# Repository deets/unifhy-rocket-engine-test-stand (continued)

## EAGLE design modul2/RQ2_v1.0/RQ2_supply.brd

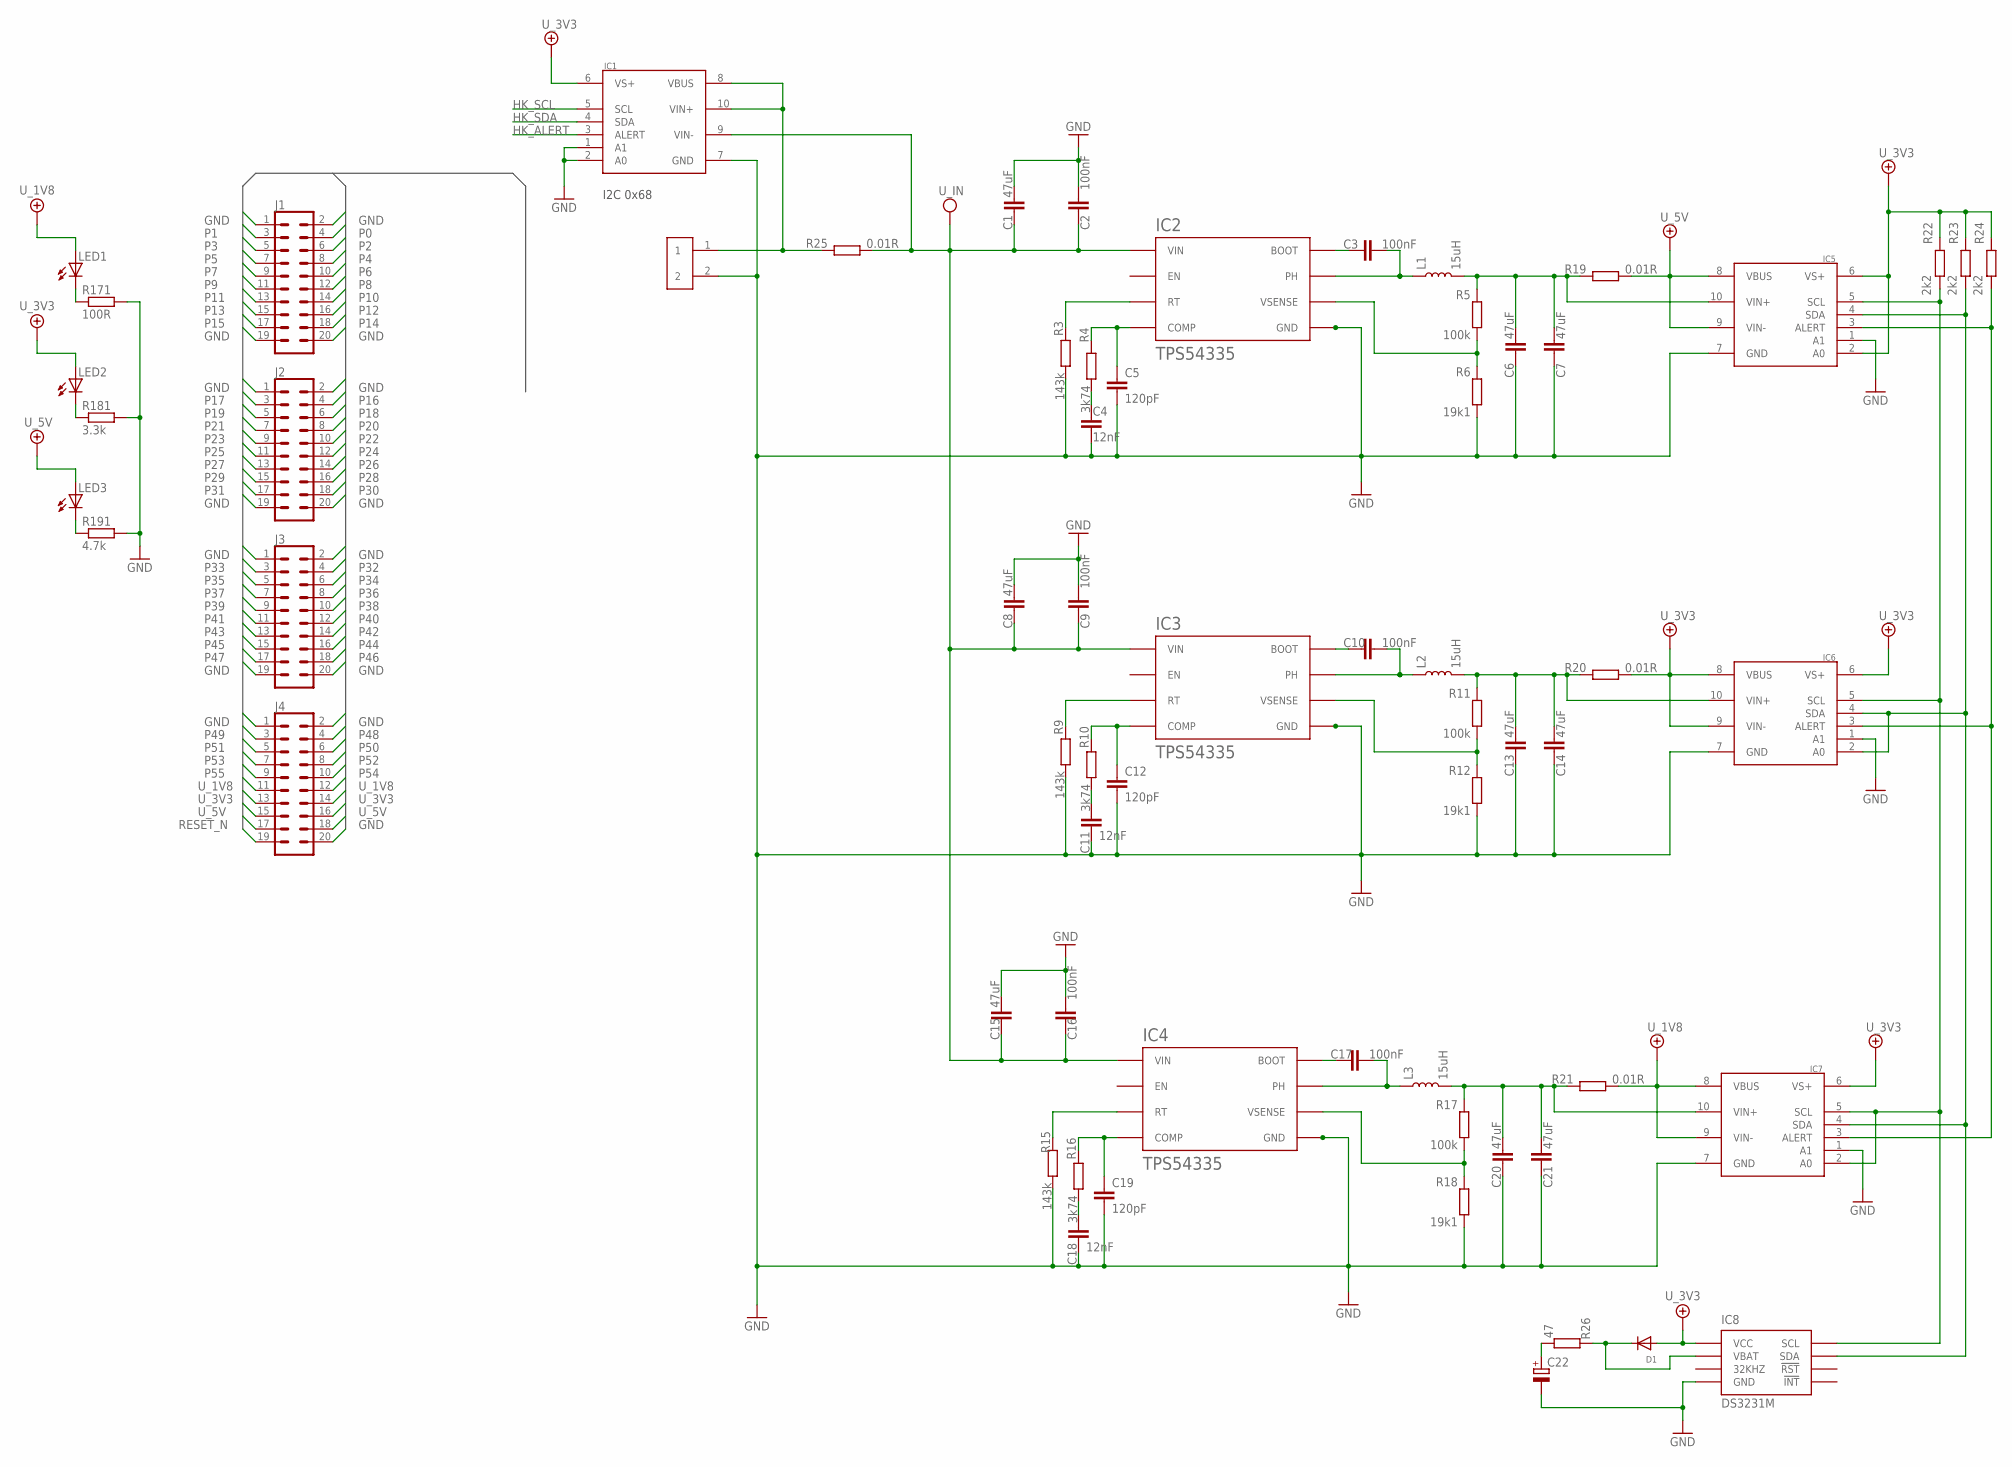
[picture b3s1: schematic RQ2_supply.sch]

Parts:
C1, C6, C7, C8, C13, C14, C15, C20, C21: 47uF; 1206
C2, C9, C16: 100nF; 0603
C3, C10, C17: 100nF; 0402
C4, C11, C18: 12nF; C0402
C5, C12, C19: 120pF; C0402
C22: CPOL-EUDHL_21.5; DHL_21.5
D1: DIODESOD-123; SOD-123
IC1, IC5, IC6, IC7: INA226; VSSOP-10
IC2, IC3, IC4: TPS54335ADRCR; VSON-10
IC8: DS3231M; SO-8
J1, J2, J3, J4: CONN_10X2; 2X10
L1, L2, L3: 15uH; YSPIA0850
LED1, LED2, LED3: LEDSML0805; SML0805
R3, R9, R15: 143k; R0402
R4, R10, R16: 3k74; R0402
R5, R11, R17: 100k; R0402
R6, R12, R18: 19k1; R0402
R19, R20, R21, R25: 0.01R; R1206
R22, R23, R24: 2k2; R0402
R26: 47; R0603
R171: 100R; R0805
R181: 3.3k; R0805
R191: 4.7k; R0805
U$1: XT_CONN; XT30_PCB

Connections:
DCDC_BOOT: C3.2, IC2.9 (BOOT)
DCDC_BOOT1: C10.2, IC3.9 (BOOT)
DCDC_BOOT2: C17.2, IC4.9 (BOOT)
DCDC_COMP: C5.1, IC2.7 (COMP), R4.1
DCDC_COMP1: C12.1, IC3.7 (COMP), R10.1
DCDC_COMP2: C19.1, IC4.7 (COMP), R16.1
DCDC_PH: C3.1, IC2.2 (PH), L1.1
DCDC_PH1: C10.1, IC3.2 (PH), L2.1
DCDC_PH2: C17.1, IC4.2 (PH), L3.1
DCDC_RT: IC2.10 (RT), R3.1
DCDC_RT1: IC3.10 (RT), R9.1
DCDC_RT2: IC4.10 (RT), R15.1
GND: C1.2, C2.1, C4.2, C5.2, C6.1, C7.1, C8.2, C9.1, C11.2, C12.2, C13.1, C14.1, C15.2, C16.1, C18.2, C19.2, C20.1, C21.1, C22.-, IC1.1 (A1), IC1.2 (A0), IC1.7 (GND), IC2.3 (GND), IC2.4 (GND), IC2.5 (GND), IC2.11 (GND), IC3.3 (GND), IC3.4 (GND), IC3.5 (GND), IC3.11 (GND), IC4.3 (GND), IC4.4 (GND), IC4.5 (GND), IC4.11 (GND), IC5.1 (A1), IC5.7 (GND), IC6.1 (A1), IC6.7 (GND), IC7.1 (A1), IC7.7 (GND), IC8.5 (GND), J1.1, J1.2, J1.19, J1.20, J2.1, J2.2, J2.19, J2.20, J3.1, J3.2, J3.19, J3.20, J4.1, J4.2, J4.18, R3.2, R6.1, R9.2, R12.1, R15.2, R18.1, R171.2, R181.2, R191.2, U$1.2
HK_ALERT: IC1.3 (ALERT), IC5.3 (ALERT), IC6.3 (ALERT), IC7.3 (ALERT), R24.1
HK_SCL: IC1.5 (SCL), IC5.5 (SCL), IC6.5 (SCL), IC7.2 (A0), IC7.5 (SCL), IC8.8 (SCL), R22.1
HK_SDA: IC1.4 (SDA), IC5.4 (SDA), IC6.2 (A0), IC6.4 (SDA), IC7.4 (SDA), IC8.7 (SDA), R23.1
unnamed: C4.1, R4.2
unnamed: LED1.C, R171.1
unnamed: LED2.C, R181.1
unnamed: LED3.C, R191.1
unnamed: C11.1, R10.2
unnamed: C18.1, R16.2
P0: J1.4
P1: J1.3
P2: J1.6
P3: J1.5
P4: J1.8
P5: J1.7
P6: J1.10
P7: J1.9
P8: J1.12
P9: J1.11
P10: J1.14
P11: J1.13
P12: J1.16
P13: J1.15
P14: J1.18
P15: J1.17
P16: J2.4
P17: J2.3
P18: J2.6
P19: J2.5
P20: J2.8
P21: J2.7
P22: J2.10
P23: J2.9
P24: J2.12
P25: J2.11
P26: J2.14
P27: J2.13
P28: J2.16
P29: J2.15
P30: J2.18
P31: J2.17
P32: J3.4
P33: J3.3
P34: J3.6
P35: J3.5
P36: J3.8
P37: J3.7
P38: J3.10
P39: J3.9
P40: J3.12
P41: J3.11
P42: J3.14
P43: J3.13
P44: J3.16
P45: J3.15
P46: J3.18
P47: J3.17
P48: J4.4
P49: J4.3
P50: J4.6
P51: J4.5
P52: J4.8
P53: J4.7
P54: J4.10
P55: J4.9
RESET_N: J4.17
RXD: J4.20
TXD: J4.19
U0_1V8: C20.2, C21.2, IC7.10 (VIN+), L3.2, R17.2, R21.2
U0_3V3: C13.2, C14.2, IC6.10 (VIN+), L2.2, R11.2, R20.2
U0_5V: C6.2, C7.2, IC5.10 (VIN+), L1.2, R5.2, R19.2
U0_IN: IC1.8 (VBUS), IC1.10 (VIN+), R25.2, U$1.1
U_1V8: IC7.8 (VBUS), IC7.9 (VIN-), J4.11, J4.12, LED1.A, R21.1
U_3V3: D1.A, IC5.2 (A0), IC6.6 (VS+), IC6.8 (VBUS), IC6.9 (VIN-), IC7.6 (VS+), IC8.2 (VCC), J4.13, J4.14, LED2.A, R20.1, R22.2, R23.2, R24.2
U_5V: IC5.8 (VBUS), IC5.9 (VIN-), J4.15, J4.16, LED3.A, R19.1
U_IN: C1.1, C2.2, C8.1, C9.2, C15.1, C16.2, IC1.9 (VIN-), IC2.1 (VIN), IC3.1 (VIN), IC4.1 (VIN), R25.1
VBAT1: D1.C, IC8.6 (VBAT), R26.1
VCAP: C22.+, R26.2
VSENSE_1V8: IC4.6 (VSENSE), R17.1, R18.2
VSENSE_3V3: IC3.6 (VSENSE), R11.1, R12.2
VSENSE_5V: IC2.6 (VSENSE), R5.1, R6.2

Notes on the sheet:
I2C 0x68

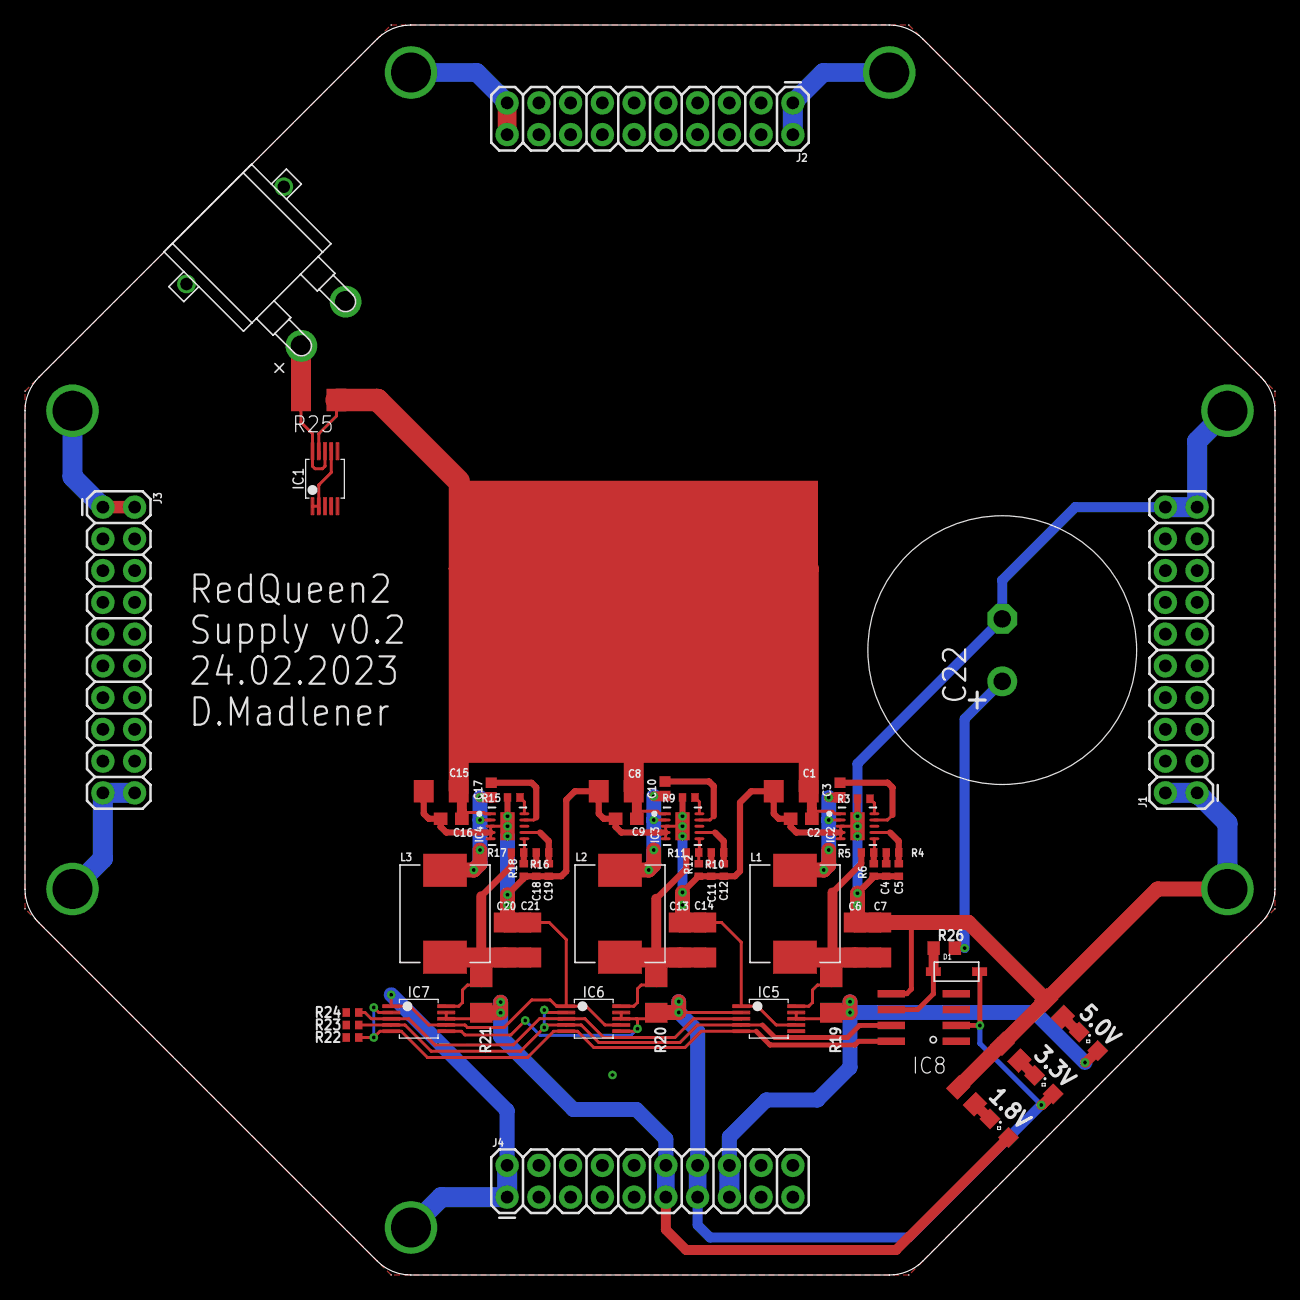
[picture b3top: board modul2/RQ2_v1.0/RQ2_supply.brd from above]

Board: 2 copper layers, 100.0 x 100.0 mm, 65 parts (0 on the bottom side), 35 nets.

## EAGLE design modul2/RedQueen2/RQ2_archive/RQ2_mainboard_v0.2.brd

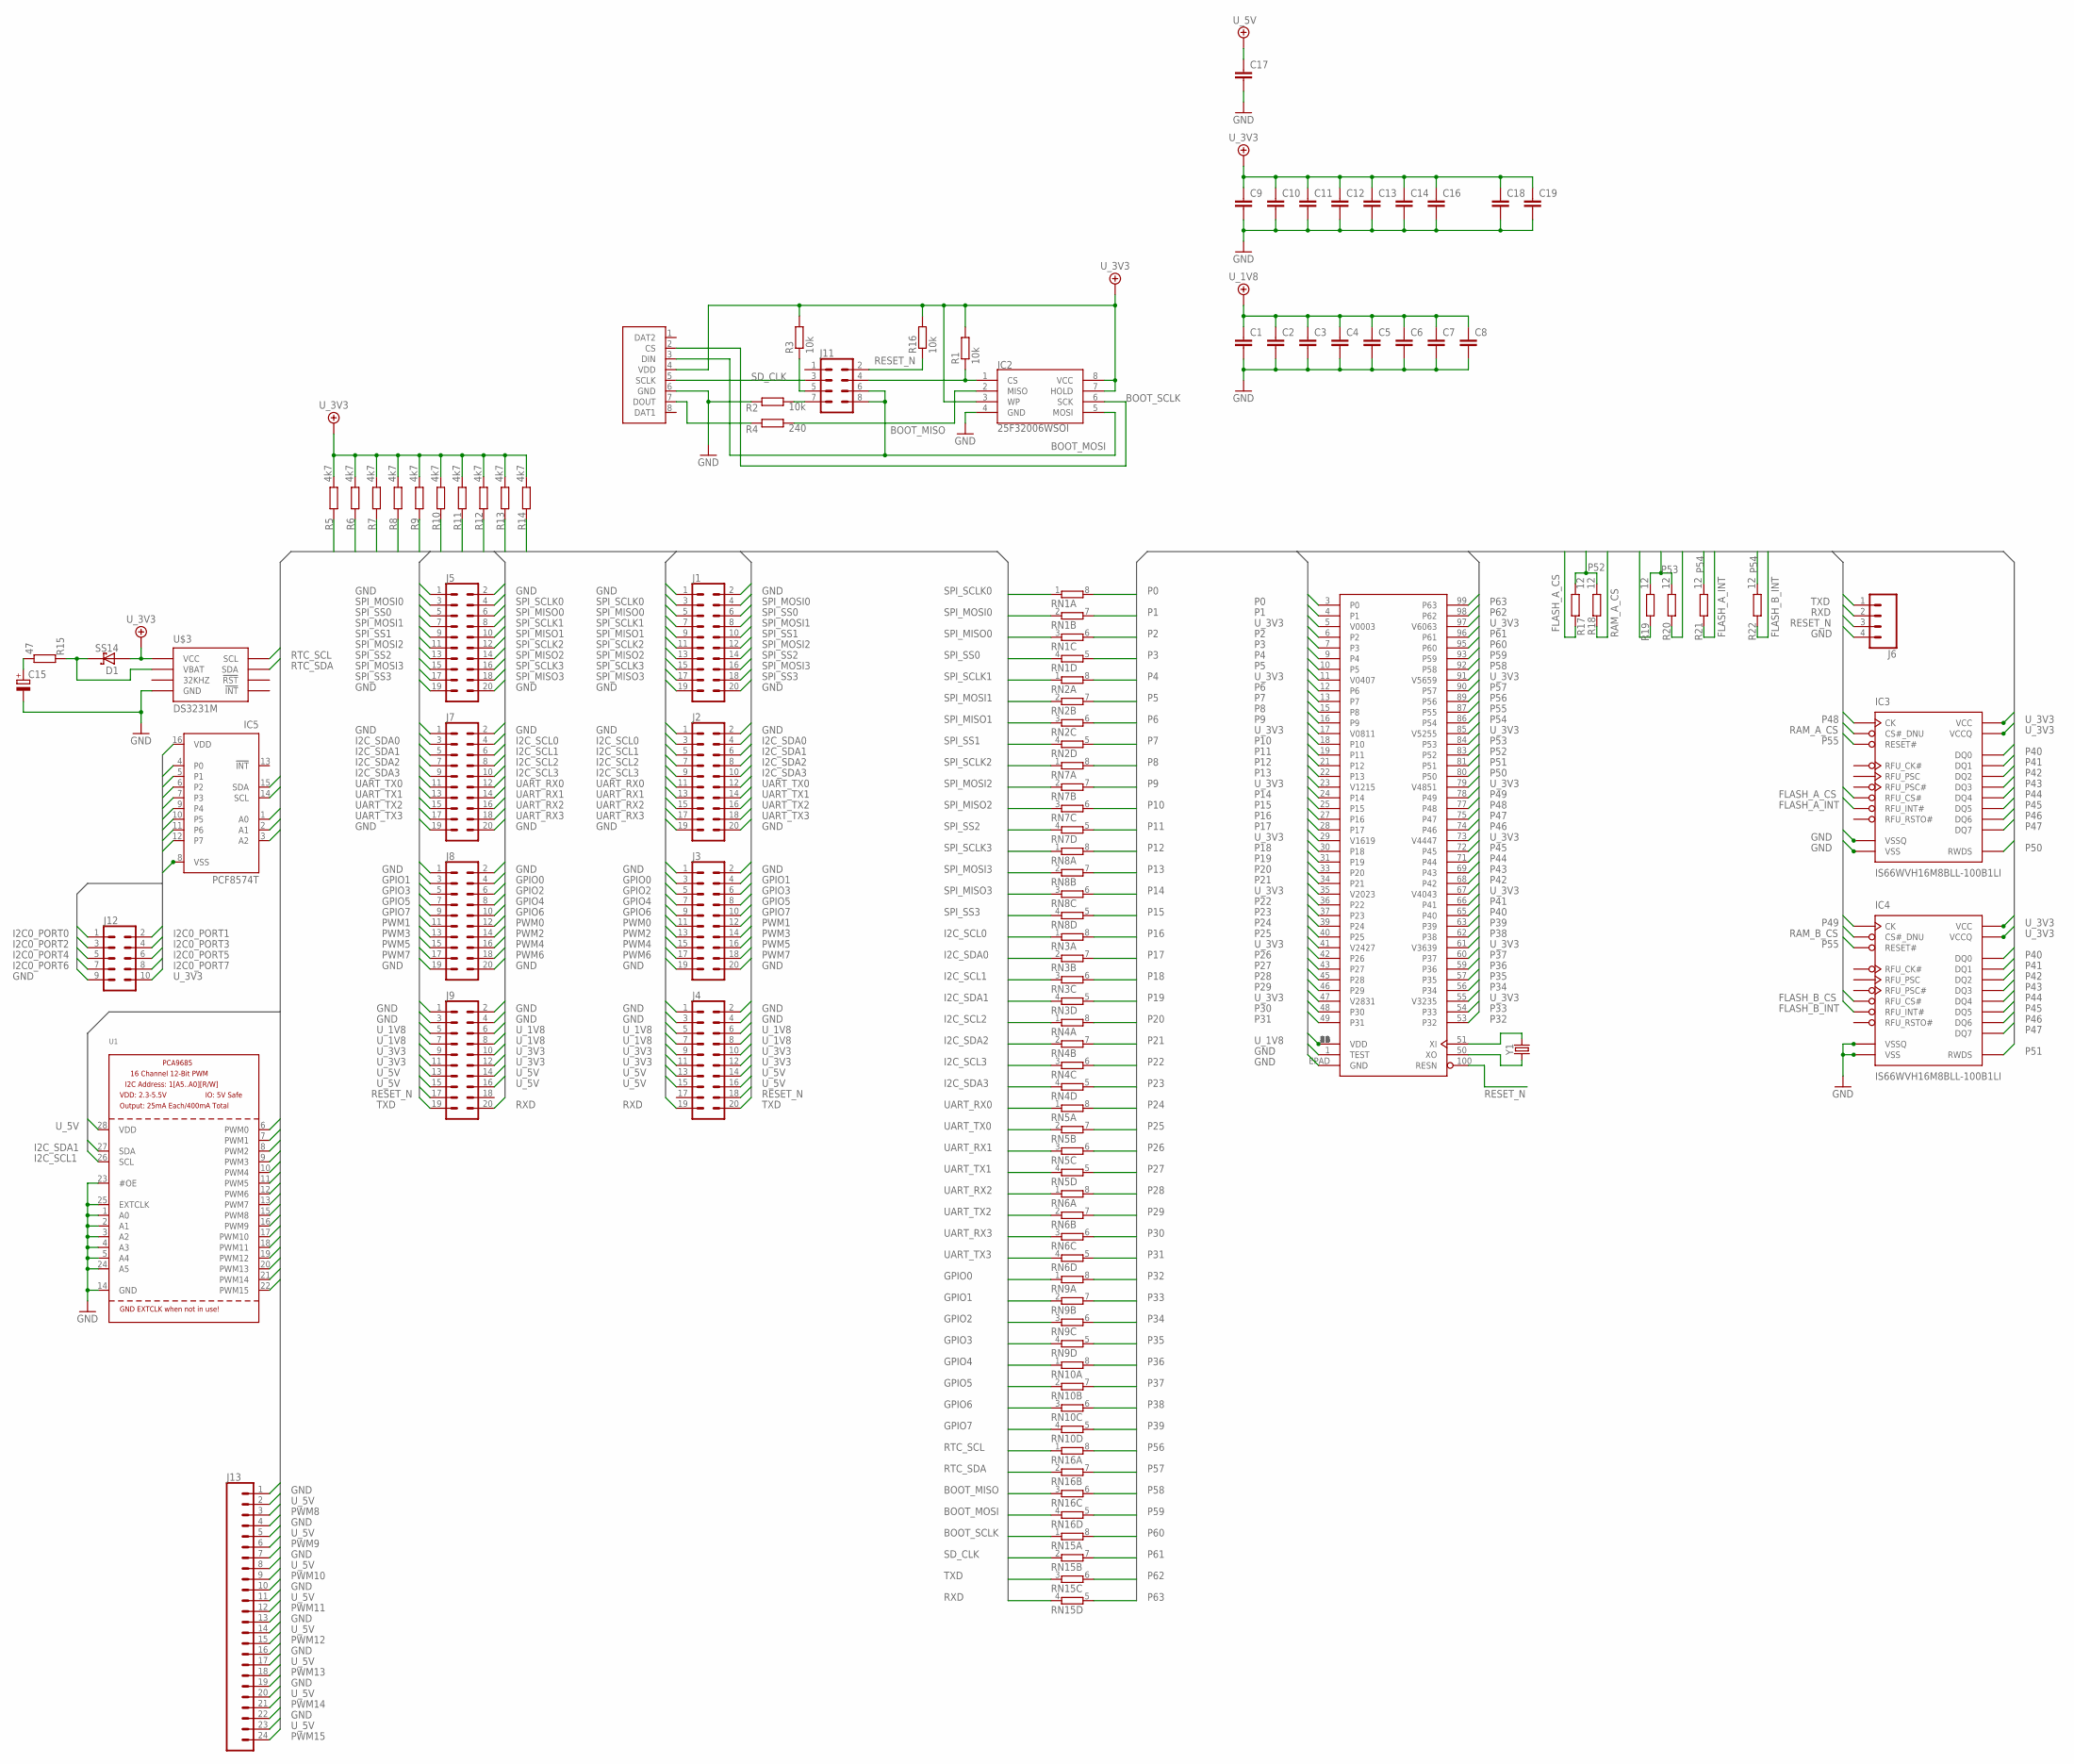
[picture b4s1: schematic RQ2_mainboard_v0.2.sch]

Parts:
C1, C2, C3, C4, C5, C6, C7, C8, C9, C10, C11, C12, C13, C14, C16, C17, C18, C19: C-EUC0805; C0805
C15: CPOL-EUDHL_21.5; DHL_21.5
D1: SS14; SMA_403D
IC1: P2X8C4M64P; TQFP100
IC2: 25F32006WSOI; SO08-EIAJ
IC3, IC4: IS66WVH16M8BLL-100B1LI; BGA-24
IC5: PCF8574T; SO16W
J1, J2, J3, J4, J5, J7, J8, J9: CONN_10X2SMT; 2X10_SMT
J6: CONN_04; 1X04
J11: CONN_04X2; 2X4
J12: CONN_05X2SHD; 2X5-SHROUDED
J13: CONN_24SERVO_8; 3X8
R1, R2, R3, R16: 10k; R0603
R4: 240; R0603
R5, R6, R7, R8, R9, R10, R11, R12, R13, R14: 4k7; R0603
R15: 47; R0603
R17, R18, R19, R20, R21, R22: 12; R0402
RN1, RN2, RN3, RN4, RN5, RN6, RN7, RN8, RN9, RN10, RN15, RN16: 4R-N0603-ARV; 0603-ARV
U1: PCA9685; TSSOP28
U$2: MICRO_SD_CONNECTORMOLEX_HINGE; MICRO_SD
U$3: DS3231M; SO-8
Y1: CRYSTALSMD-5X3.2-2PAD; CRYSTAL-SMD-5X3.2-2PAD

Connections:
BOOT_MISO: IC2.2 (MISO), R4.1, RN16.3 (1)
BOOT_MOSI: IC2.5 (MOSI), J11.6, J11.8, RN16.4 (1), U$2.3 (DIN)
BOOT_SCLK: IC2.6 (SCK), RN15.1, U$2.2 (CS)
FLASH_A_CS: IC3.C2 (RFU_CS#), R17.2
FLASH_A_INT: IC3.A5 (RFU_INT#), R21.2
FLASH_B_CS: IC4.C2 (RFU_CS#), R19.2
FLASH_B_INT: IC4.A5 (RFU_INT#), R22.2
FLASH_CS: IC2.1 (CS), J11.4, R1.1
GND: C1.2, C2.2, C3.2, C4.2, C5.2, C6.2, C7.2, C8.2, C9.2, C10.2, C11.2, C12.2, C13.2, C14.2, C15.-, C16.2, C17.2, C18.2, C19.2, IC1.1 (TEST), IC1.EPAD (GND), IC2.4 (GND), IC3.B3 (VSS), IC3.C1 (VSSQ), IC3.E5 (VSSQ), IC4.B3 (VSS), IC4.C1 (VSSQ), IC4.E5 (VSSQ), IC5.1 (A0), IC5.2 (A1), IC5.3 (A2), IC5.8 (VSS), J1.1, J1.2, J1.19, J1.20, J2.1, J2.2, J2.19, J2.20, J3.1, J3.2, J3.19, J3.20, J4.1, J4.2, J4.3, J4.4, J5.1, J5.2, J5.19, J5.20, J6.4, J7.1, J7.2, J7.19, J7.20, J8.1, J8.2, J8.19, J8.20, J9.1, J9.2, J9.3, J9.4, J12.9, J13.1, J13.4, J13.7, J13.10, J13.13, J13.16, J13.19, J13.22, R2.2, U1.1 (A0), U1.2 (A1), U1.3 (A2), U1.4 (A3), U1.5 (A4), U1.14 (GND), U1.23 (#OE), U1.24 (A5), U1.25 (EXTCLK), U$2.6 (GND), U$3.5 (GND)
GPIO0: J3.3, J8.4, RN9.1
GPIO1: J3.4, J8.3, RN9.2 (1)
GPIO2: J3.5, J8.6, RN9.3 (1)
GPIO3: J3.6, J8.5, RN9.4 (1)
GPIO4: J3.7, J8.8, RN10.1
GPIO5: J3.8, J8.7, RN10.2 (1)
GPIO6: J3.9, J8.10, RN10.3 (1)
GPIO7: J3.10, J8.9, RN10.4 (1)
I2C0_PORT0: IC5.4 (P0), J12.1
I2C0_PORT1: IC5.5 (P1), J12.2
I2C0_PORT2: IC5.6 (P2), J12.3
I2C0_PORT3: IC5.7 (P3), J12.4
I2C0_PORT4: IC5.9 (P4), J12.5
I2C0_PORT5: IC5.10 (P5), J12.6
I2C0_PORT6: IC5.11 (P6), J12.7
I2C0_PORT7: IC5.12 (P7), J12.8
I2C_SCL0: IC5.14 (SCL), J2.3, J7.4, R5.1, RN3.1
I2C_SCL1: J2.5, J7.6, R7.1, RN3.3 (1), U1.26 (SCL)
I2C_SCL2: J2.7, J7.8, R9.1, RN4.1
I2C_SCL3: J2.9, J7.10, R11.1, RN4.3 (1)
I2C_SDA0: IC5.15 (SDA), J2.4, J7.3, R6.1, RN3.2 (1)
I2C_SDA1: J2.6, J7.5, R8.1, RN3.4 (1), U1.27 (SDA)
I2C_SDA2: J2.8, J7.7, R10.1, RN4.2 (1)
I2C_SDA3: J2.10, J7.9, R12.1, RN4.4 (1)
unnamed: J11.7, R2.1
unnamed: J11.5, R3.1
unnamed: R4.2, U$2.7 (DOUT)
P0: IC1.3 (P0), RN1.8 (2)
P1: IC1.4 (P1), RN1.7 (2)
P2: IC1.6 (P2), RN1.6 (2)
P3: IC1.7 (P3), RN1.5 (2)
P4: IC1.9 (P4), RN2.8 (2)
P5: IC1.10 (P5), RN2.7 (2)
P6: IC1.12 (P6), RN2.6 (2)
P7: IC1.13 (P7), RN2.5 (2)
P8: IC1.15 (P8), RN7.8 (2)
P9: IC1.16 (P9), RN7.7 (2)
P10: IC1.18 (P10), RN7.6 (2)
P11: IC1.19 (P11), RN7.5 (2)
P12: IC1.21 (P12), RN8.8 (2)
P13: IC1.22 (P13), RN8.7 (2)
P14: IC1.24 (P14), RN8.6 (2)
P15: IC1.25 (P15), RN8.5 (2)
P16: IC1.27 (P16), RN3.8 (2)
P17: IC1.28 (P17), RN3.7 (2)
P18: IC1.30 (P18), RN3.6 (2)
P19: IC1.31 (P19), RN3.5 (2)
P20: IC1.33 (P20), RN4.8 (2)
P21: IC1.34 (P21), RN4.7 (2)
P22: IC1.36 (P22), RN4.6 (2)
P23: IC1.37 (P23), RN4.5 (2)
P24: IC1.39 (P24), RN5.8 (2)
P25: IC1.40 (P25), RN5.7 (2)
P26: IC1.42 (P26), RN5.6 (2)
P27: IC1.43 (P27), RN5.5 (2)
P28: IC1.45 (P28), RN6.8 (2)
P29: IC1.46 (P29), RN6.7 (2)
P30: IC1.48 (P30), RN6.6 (2)
P31: IC1.49 (P31), RN6.5 (2)
P32: IC1.53 (P32), RN9.8 (2)
P33: IC1.54 (P33), RN9.7 (2)
P34: IC1.56 (P34), RN9.6 (2)
P35: IC1.57 (P35), RN9.5 (2)
P36: IC1.59 (P36), RN10.8 (2)
P37: IC1.60 (P37), RN10.7 (2)
P38: IC1.62 (P38), RN10.6 (2)
P39: IC1.63 (P39), RN10.5 (2)
P40: IC1.65 (P40), IC3.D3 (DQ0), IC4.D3 (DQ0)
P41: IC1.66 (P41), IC3.D2 (DQ1), IC4.D2 (DQ1)
P42: IC1.68 (P42), IC3.C4 (DQ2), IC4.C4 (DQ2)
P43: IC1.69 (P43), IC3.D4 (DQ3), IC4.D4 (DQ3)
P44: IC1.71 (P44), IC3.D5 (DQ4), IC4.D5 (DQ4)
P45: IC1.72 (P45), IC3.E3 (DQ5), IC4.E3 (DQ5)
P46: IC1.74 (P46), IC3.E2 (DQ6), IC4.E2 (DQ6)
P47: IC1.75 (P47), IC3.E1 (DQ7), IC4.E1 (DQ7)
P48: IC1.77 (P48), IC3.B2 (CK)
P49: IC1.78 (P49), IC4.B2 (CK)
P50: IC1.80 (P50), IC3.C3 (RWDS)
P51: IC1.81 (P51), IC4.C3 (RWDS)
P52: IC1.83 (P52), R17.1, R18.1
P53: IC1.84 (P53), R19.1, R20.1
P54: IC1.86 (P54), R21.1, R22.1
P55: IC1.87 (P55), IC3.A4 (RESET#), IC4.A4 (RESET#)
P56: IC1.89 (P56), RN16.8 (2)
P57: IC1.90 (P57), RN16.7 (2)
P58: IC1.92 (P58), RN16.6 (2)
P59: IC1.93 (P59), RN16.5 (2)
P60: IC1.95 (P60), RN15.8 (2)
P61: IC1.96 (P61), RN15.7 (2)
P62: IC1.98 (P62), RN15.6 (2)
P63: IC1.99 (P63), RN15.5 (2)
PWM0: J3.11, J8.12, U1.6 (PWM0)
PWM1: J3.12, J8.11, U1.7 (PWM1)
PWM2: J3.13, J8.14, U1.8 (PWM2)
PWM3: J3.14, J8.13, U1.9 (PWM3)
PWM4: J3.15, J8.16, U1.10 (PWM4)
PWM5: J3.16, J8.15, U1.11 (PWM5)
PWM6: J3.17, J8.18, U1.12 (PWM6)
PWM7: J3.18, J8.17, U1.13 (PWM7)
PWM8: J13.3, U1.15 (PWM8)
PWM9: J13.6, U1.16 (PWM9)
PWM10: J13.9, U1.17 (PWM10)
PWM11: J13.12, U1.18 (PWM11)
PWM12: J13.15, U1.19 (PWM12)
PWM13: J13.18, U1.20 (PWM13)
PWM14: J13.21, U1.21 (PWM14)
PWM15: J13.24, U1.22 (PWM15)
RAM_A_CS: IC3.A3 (CS#_DNU), R18.2
RAM_B_CS: IC4.A3 (CS#_DNU), R20.2
RESET_N: IC1.100 (RESN), J4.18, J6.3, J9.17, J11.2, R16.1
RTC_SCL: R13.1, RN16.1, U$3.8 (SCL)
RTC_SDA: R14.1, RN16.2 (1), U$3.7 (SDA)
RXD: J4.19, J6.2, J9.20, RN15.4 (1)
SD_CLK: J11.3, RN15.2 (1), U$2.5 (SCLK)
SPI_MISO0: J1.5, J5.6, RN1.3 (1)
SPI_MISO1: J1.9, J5.10, RN2.3 (1)
SPI_MISO2: J1.13, J5.14, RN7.3 (1)
SPI_MISO3: J1.17, J5.18, RN8.3 (1)
SPI_MOSI0: J1.4, J5.3, RN1.2 (1)
SPI_MOSI1: J1.8, J5.7, RN2.2 (1)
SPI_MOSI2: J1.12, J5.11, RN7.2 (1)
SPI_MOSI3: J1.16, J5.15, RN8.2 (1)
SPI_SCLK0: J1.3, J5.4, RN1.1
SPI_SCLK1: J1.7, J5.8, RN2.1
SPI_SCLK2: J1.11, J5.12, RN7.1
SPI_SCLK3: J1.15, J5.16, RN8.1
SPI_SS0: J1.6, J5.5, RN1.4 (1)
SPI_SS1: J1.10, J5.9, RN2.4 (1)
SPI_SS2: J1.14, J5.13, RN7.4 (1)
SPI_SS3: J1.18, J5.17, RN8.4 (1)
TXD: J4.20, J6.1, J9.19, RN15.3 (1)
UART_RX0: J2.11, J7.12, RN5.1
UART_RX1: J2.13, J7.14, RN5.3 (1)
UART_RX2: J2.15, J7.16, RN6.1
UART_RX3: J2.17, J7.18, RN6.3 (1)
UART_TX0: J2.12, J7.11, RN5.2 (1)
UART_TX1: J2.14, J7.13, RN5.4 (1)
UART_TX2: J2.16, J7.15, RN6.2 (1)
UART_TX3: J2.18, J7.17, RN6.4 (1)
U_1V8: C1.1, C2.1, C3.1, C4.1, C5.1, C6.1, C7.1, C8.1, IC1.2 (VDD), IC1.8 (VDD), IC1.14 (VDD), IC1.20 (VDD), IC1.26 (VDD), IC1.32 (VDD), IC1.38 (VDD), IC1.44 (VDD), IC1.52 (VDD), IC1.58 (VDD), IC1.64 (VDD), IC1.70 (VDD), IC1.76 (VDD), IC1.82 (VDD), IC1.88 (VDD), IC1.94 (VDD), J4.5, J4.6, J4.7, J4.8, J9.5, J9.6, J9.7, J9.8
U_3V3: C9.1, C10.1, C11.1, C12.1, C13.1, C14.1, C16.1, C18.1, C19.1, D1.A, IC1.5 (V0003), IC1.11 (V0407), IC1.17 (V0811), IC1.23 (V1215), IC1.29 (V1619), IC1.35 (V2023), IC1.41 (V2427), IC1.47 (V2831), IC1.55 (V3235), IC1.61 (V3639), IC1.67 (V4043), IC1.73 (V4447), IC1.79 (V4851), IC1.85 (V5255), IC1.91 (V5659), IC1.97 (V6063), IC2.3 (WP), IC2.7 (HOLD), IC2.8 (VCC), IC3.B4 (VCC), IC3.D1 (VCCQ), IC3.E4 (VCCQ), IC4.B4 (VCC), IC4.D1 (VCCQ), IC4.E4 (VCCQ), IC5.16 (VDD), J4.9, J4.10, J4.11, J4.12, J9.9, J9.10, J9.11, J9.12, J12.10, R1.2, R3.2, R5.2, R6.2, R7.2, R8.2, R9.2, R10.2, R11.2, R12.2, R13.2, R14.2, R16.2, U$2.4 (VDD), U$3.2 (VCC)
U_5V: C17.1, J4.13, J4.14, J4.15, J4.16, J9.13, J9.14, J9.15, J9.16, J13.2, J13.5, J13.8, J13.11, J13.14, J13.17, J13.20, J13.23, U1.28 (VDD)
VBAT: D1.C, R15.1, U$3.6 (VBAT)
VCAP: C15.+, R15.2
XIN: IC1.51 (XI), Y1.P$2 (2)
XOUT: IC1.50 (XO), Y1.P$1 (1)

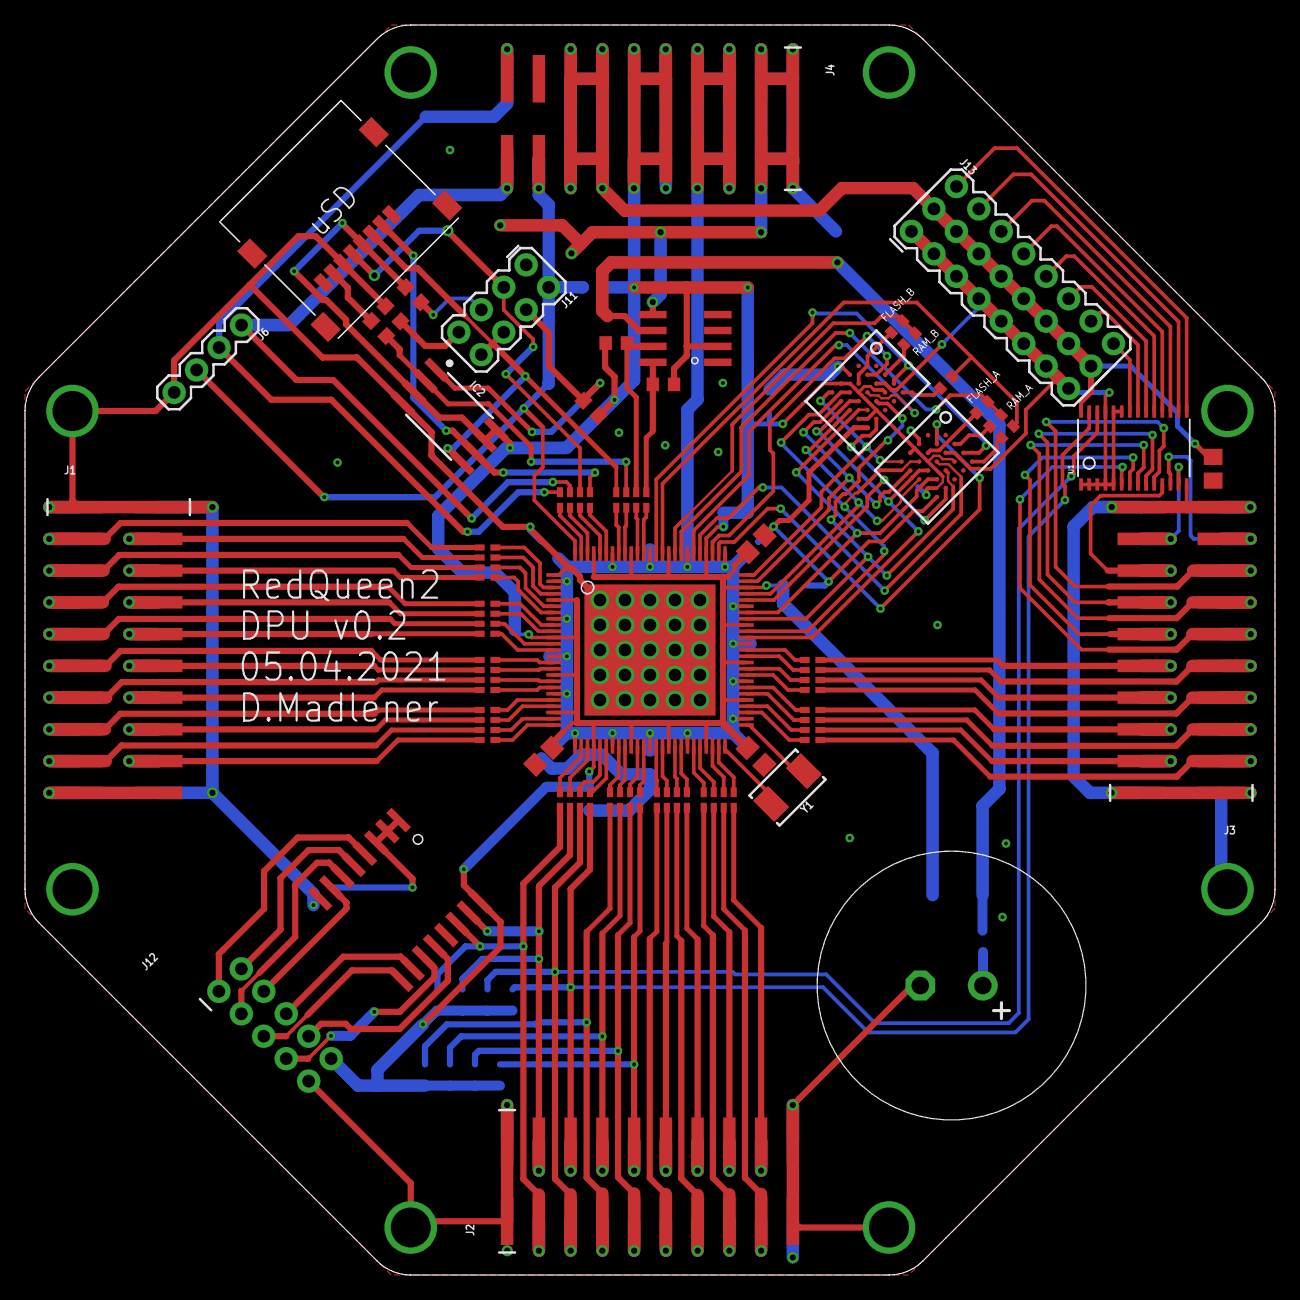
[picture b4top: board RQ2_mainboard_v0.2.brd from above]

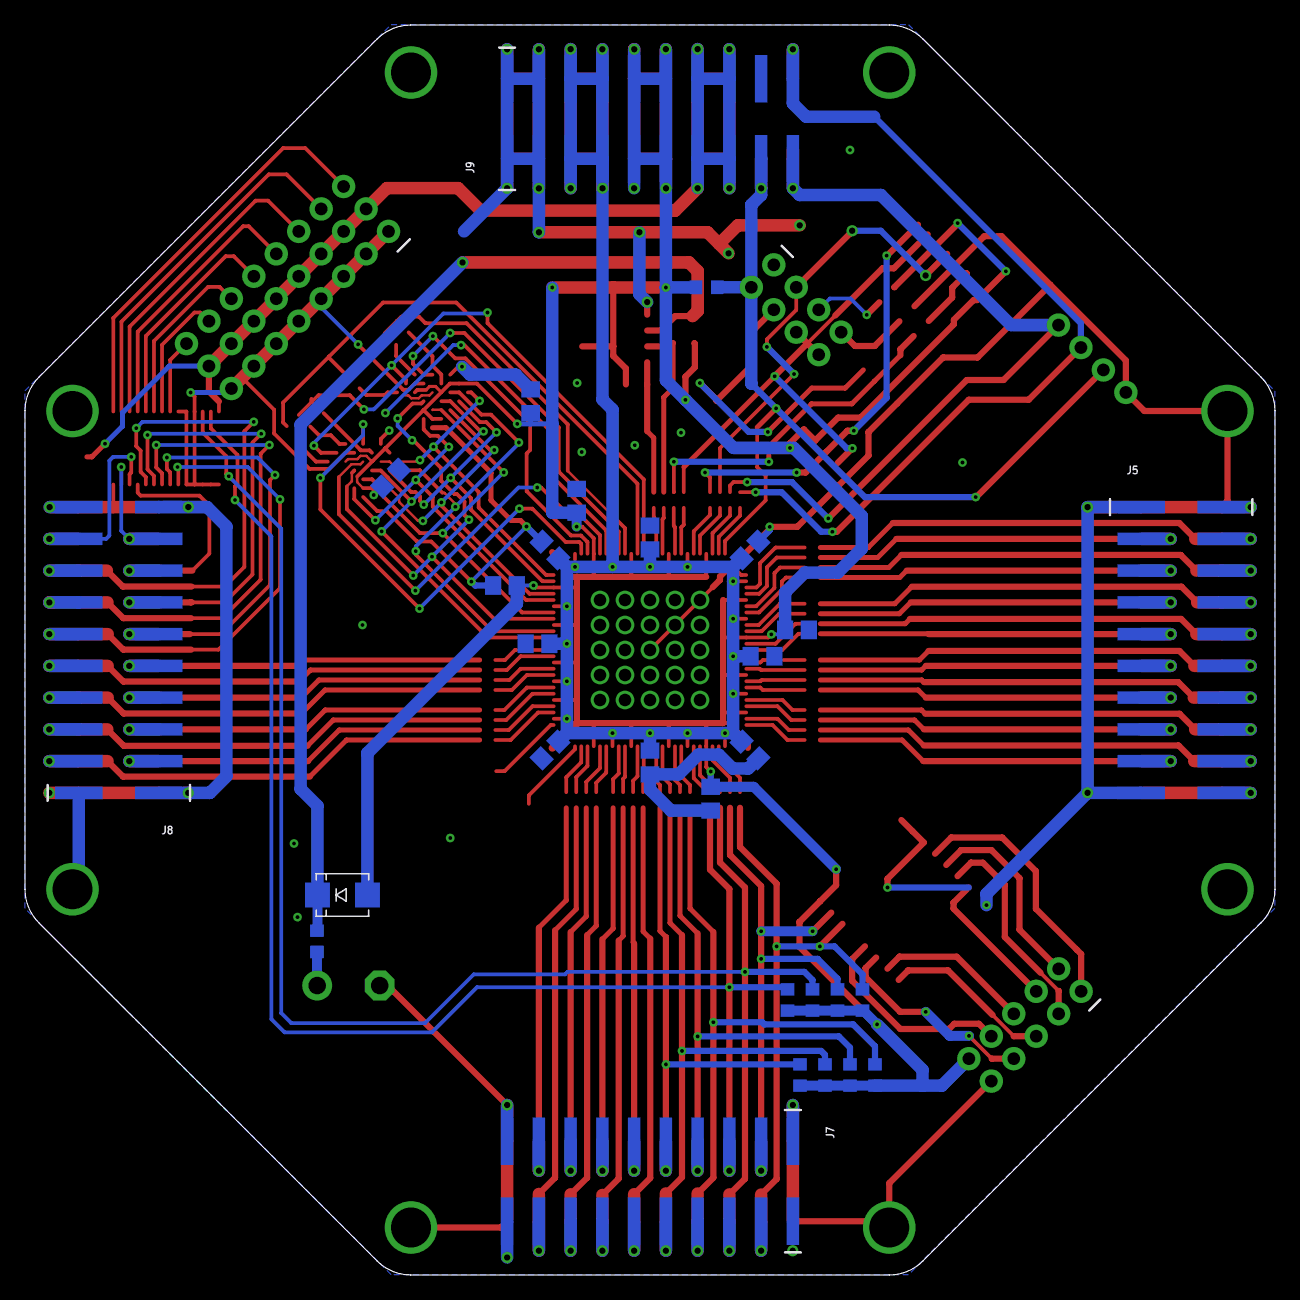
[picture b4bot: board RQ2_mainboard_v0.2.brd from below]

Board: 2 copper layers, 100.0 x 100.0 mm, 75 parts (29 on the bottom side), 155 nets.

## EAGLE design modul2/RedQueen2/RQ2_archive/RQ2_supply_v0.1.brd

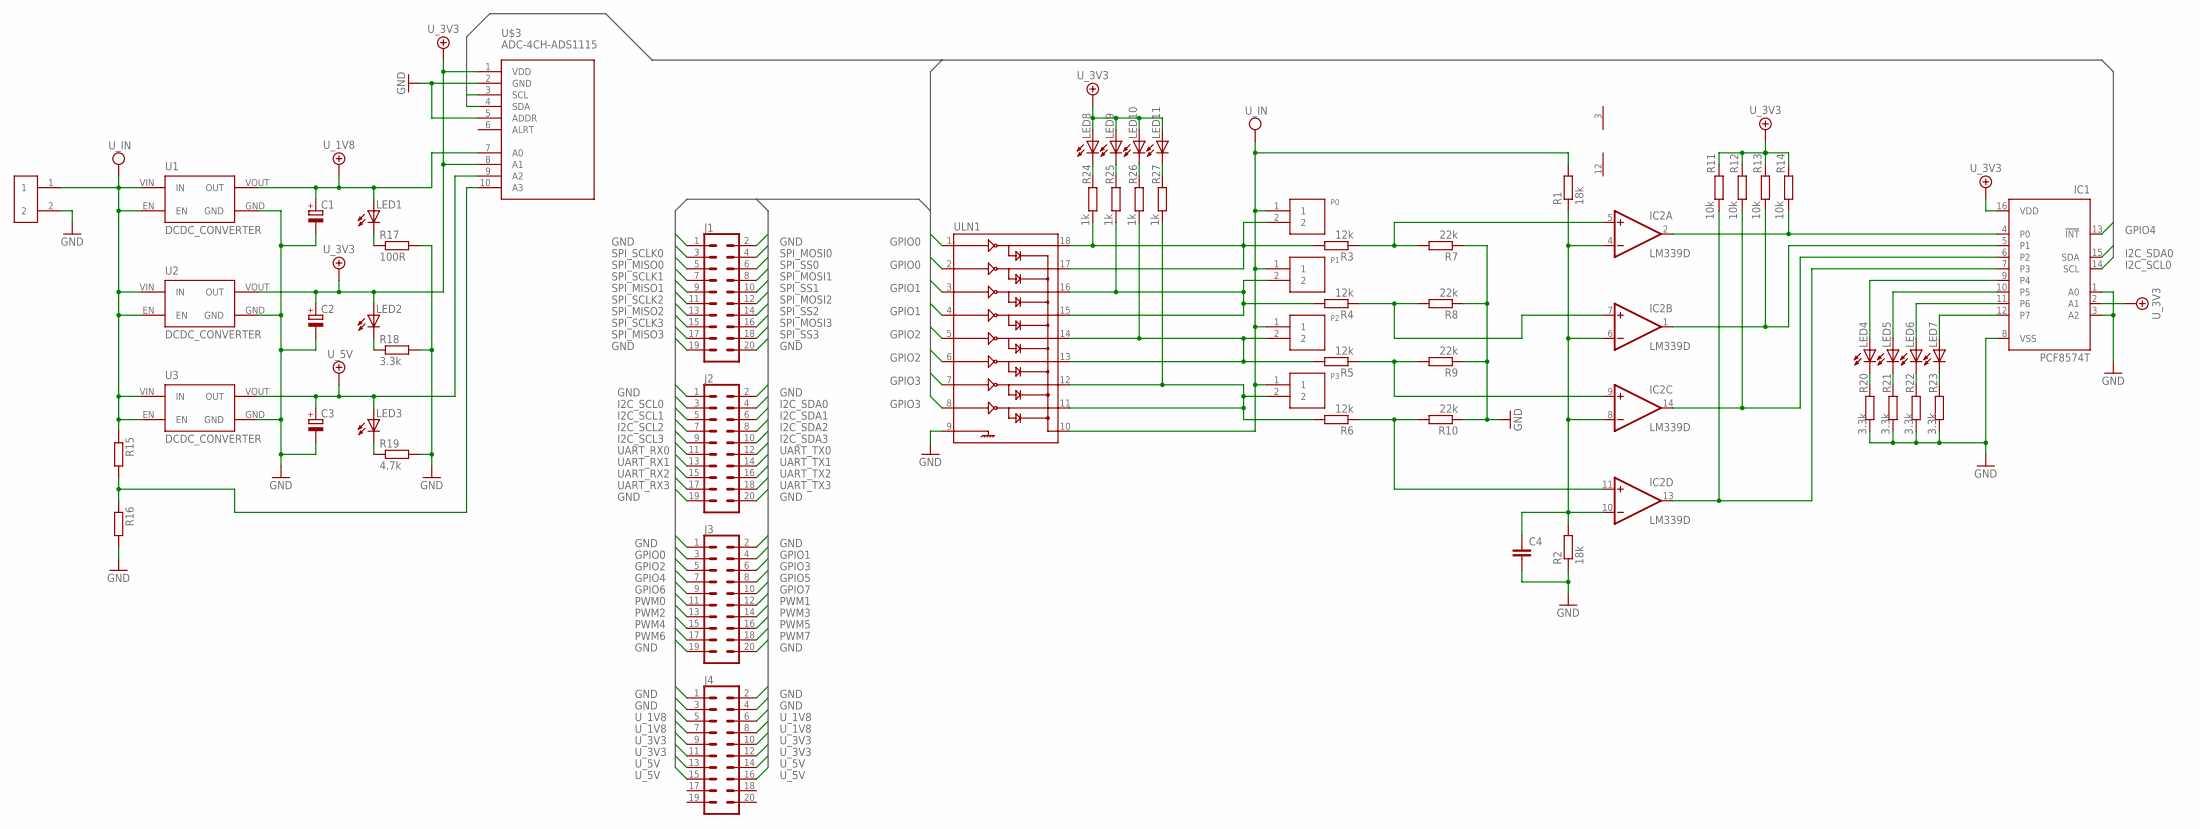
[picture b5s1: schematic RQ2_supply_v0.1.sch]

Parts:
C1, C2, C3: CPOL-EUSANYO_E9; SANYO-OSCON_E9
C4: C-EUC0805; C0805
IC1: PCF8574T; SO16W
IC2: LM339D; SO14
J1, J2, J3, J4: CONN_10X2; 2X10
LED1, LED2, LED3, LED4, LED5, LED6, LED7, LED8, LED9, LED10, LED11: LEDSML0805; SML0805
P0, P1, P2, P3: 2PIN; B2B-PH-K-S
R1, R2: 18k; R0805
R3, R4, R5, R6: 12k; R0805
R7, R8, R9, R10: 22k; R0805
R11, R12, R13, R14: 10k; R0805
R15, R16: R-EU_R0805; R0805
R17: 100R; R0805
R18, R20, R21, R22, R23: 3.3k; R0805
R19: 4.7k; R0805
R24, R25, R26, R27: 1k; R0805
U1, U2, U3: DCDC_CONVERTER
U$1: XT_CONN; XT30_PCB
U$3: ADC-4CH-ADS1115
ULN1: ULN2803SOICW; SO18L

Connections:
COMPARE: C4.1, IC2.4 (-IN), IC2.6 (-IN), IC2.8 (-IN), IC2.10 (-IN), R1.1, R2.2
GND: C1.-, C2.-, C3.-, C4.2, IC1.1 (A0), IC1.3 (A2), IC1.8 (VSS), IC2.12 (GND), J1.1, J1.2, J1.19, J1.20, J2.1, J2.2, J2.19, J2.20, J3.1, J3.2, J3.19, J3.20, J4.1, J4.2, J4.3, J4.4, R2.1, R7.1, R8.1, R9.1, R10.1, R16.2, R17.2, R18.2, R19.2, R20.1, R21.1, R22.1, R23.1, U1.GND, U2.GND, U3.GND, U$1.2, U$3.2 (GND), U$3.5 (ADDR), ULN1.9
GPIO0: J3.3, ULN1.1, ULN1.2
GPIO1: J3.4, ULN1.3, ULN1.4
GPIO2: J3.5, ULN1.5, ULN1.6
GPIO3: J3.6, ULN1.7, ULN1.8
GPIO4: IC1.13 (!INT), J3.7
GPIO5: J3.8
GPIO6: J3.9
GPIO7: J3.10
I2C_SCL0: IC1.14 (SCL), J2.3, U$3.3 (SCL)
I2C_SCL1: J2.5
I2C_SCL2: J2.7
I2C_SCL3: J2.9
I2C_SDA0: IC1.15 (SDA), J2.4, U$3.4 (SDA)
I2C_SDA1: J2.6
I2C_SDA2: J2.8
I2C_SDA3: J2.10
LED4: LED4.C, R20.2
LED5: LED5.C, R21.2
LED6: LED6.C, R22.2
LED7: LED7.C, R23.2
unnamed: R15.2, R16.1, U$3.10 (A3)
unnamed: LED1.C, R17.1
unnamed: LED2.C, R18.1
unnamed: LED3.C, R19.1
unnamed: LED8.C, R24.2
unnamed: LED9.C, R25.2
unnamed: LED10.C, R26.2
unnamed: LED11.C, R27.2
NOT_BLOWN0: IC1.4 (P0), IC2.2 (OUT), R14.1
NOT_BLOWN1: IC1.5 (P1), IC2.1 (OUT), R13.1
NOT_BLOWN2: IC1.6 (P2), IC2.14 (OUT), R12.1
NOT_BLOWN3: IC1.7 (P3), IC2.13 (OUT), R11.1
P4: IC1.9 (P4), LED4.A
P5: IC1.10 (P5), LED5.A
P6: IC1.11 (P6), LED6.A
P7: IC1.12 (P7), LED7.A
PWM0: J3.11
PWM1: J3.12
PWM2: J3.13
PWM3: J3.14
PWM4: J3.15
PWM5: J3.16
PWM6: J3.17
PWM7: J3.18
PYRO0: P0.2, R3.2, R24.1, ULN1.17, ULN1.18
PYRO1: P1.2, R4.2, R25.1, ULN1.15, ULN1.16
PYRO2: P2.2, R5.2, R26.1, ULN1.13, ULN1.14
PYRO3: P3.2, R6.2, R27.1, ULN1.11, ULN1.12
PYRO_PROBE0: IC2.5 (+IN), R3.1, R7.2
PYRO_PROBE1: IC2.7 (+IN), R4.1, R8.2
PYRO_PROBE2: IC2.9 (+IN), R5.1, R9.2
PYRO_PROBE3: IC2.11 (+IN), R6.1, R10.2
SPI_MISO0: J1.5
SPI_MISO1: J1.9
SPI_MISO2: J1.13
SPI_MISO3: J1.17
SPI_MOSI0: J1.4
SPI_MOSI1: J1.8
SPI_MOSI2: J1.12
SPI_MOSI3: J1.16
SPI_SCLK0: J1.3
SPI_SCLK1: J1.7
SPI_SCLK2: J1.11
SPI_SCLK3: J1.15
SPI_SS0: J1.6
SPI_SS1: J1.10
SPI_SS2: J1.14
SPI_SS3: J1.18
UART_RX0: J2.11
UART_RX1: J2.13
UART_RX2: J2.15
UART_RX3: J2.17
UART_TX0: J2.12
UART_TX1: J2.14
UART_TX2: J2.16
UART_TX3: J2.18
U_1V8: C1.+, J4.5, J4.6, J4.7, J4.8, LED1.A, U1.VOUT (OUT), U$3.7 (A0)
U_3V3: C2.+, IC1.2 (A1), IC1.16 (VDD), J4.9, J4.10, J4.11, J4.12, LED2.A, LED8.A, LED9.A, LED10.A, LED11.A, R11.2, R12.2, R13.2, R14.2, U2.VOUT (OUT), U$3.1 (VDD), U$3.8 (A1)
U_5V: C3.+, J4.13, J4.14, J4.15, J4.16, LED3.A, U3.VOUT (OUT), U$3.9 (A2)
U_IN: P0.1, P1.1, P2.1, P3.1, R1.2, R15.1, U1.EN, U1.VIN (IN), U2.EN, U2.VIN (IN), U3.EN, U3.VIN (IN), U$1.1, ULN1.10
V+: IC2.3 (V+)
